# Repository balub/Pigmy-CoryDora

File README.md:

# Pigmy Corydora

A compact 3-key macropad built around the [Glyph Mini RP2040](https://shop.pcbcupid.com/product/gdm001). Designed for desk use as a shortcut pad, mute button, or media controller small enough to stay out of the way.

**[Build Guide →](https://www.notion.so/Pigmy-CoryDora-Build-Guide-36b9d3177a9b804fbc1ad1b240c95a71?source=copy_link)**

## Features

- 3× Cherry MX-compatible switches
- 2× WS2812B RGB LEDs
- Glyph Mini RP2040 (PCB Cupid) (RP2040, USB-C, onboard LED)
- 4× M2 mounting holes for case attachment
- Hand-solderable SMD components (1206 caps)

## Bill of Materials

| Ref | Component | Qty |
|-----|-----------|-----|
| RZ1 | Glyph Mini RP2040 (PCB Cupid) | 1 |
| SW1–SW3 | Cherry MX-compatible switch | 3 |
| D1–D2 | WS2812B LED (PLCC-4, 5×5mm) | 2 |
| R1 | 330Ω resistor (1206) | 1 |
| C1, C2 | 100nF capacitor (1206) | 2 |
| H1–H4 | M2 mounting hardware | 4 |

## PCB

Designed in KiCad 8. Gerbers can be generated from `pigmy-corydora.kicad_pcb` and sent to any PCB fab (Lions Circuit, JLCPCB, PCBWay, etc.).

## License

Hardware design files are released under [CERN-OHL-P v2](https://ohwr.org/cern_ohl_p_v2.txt).

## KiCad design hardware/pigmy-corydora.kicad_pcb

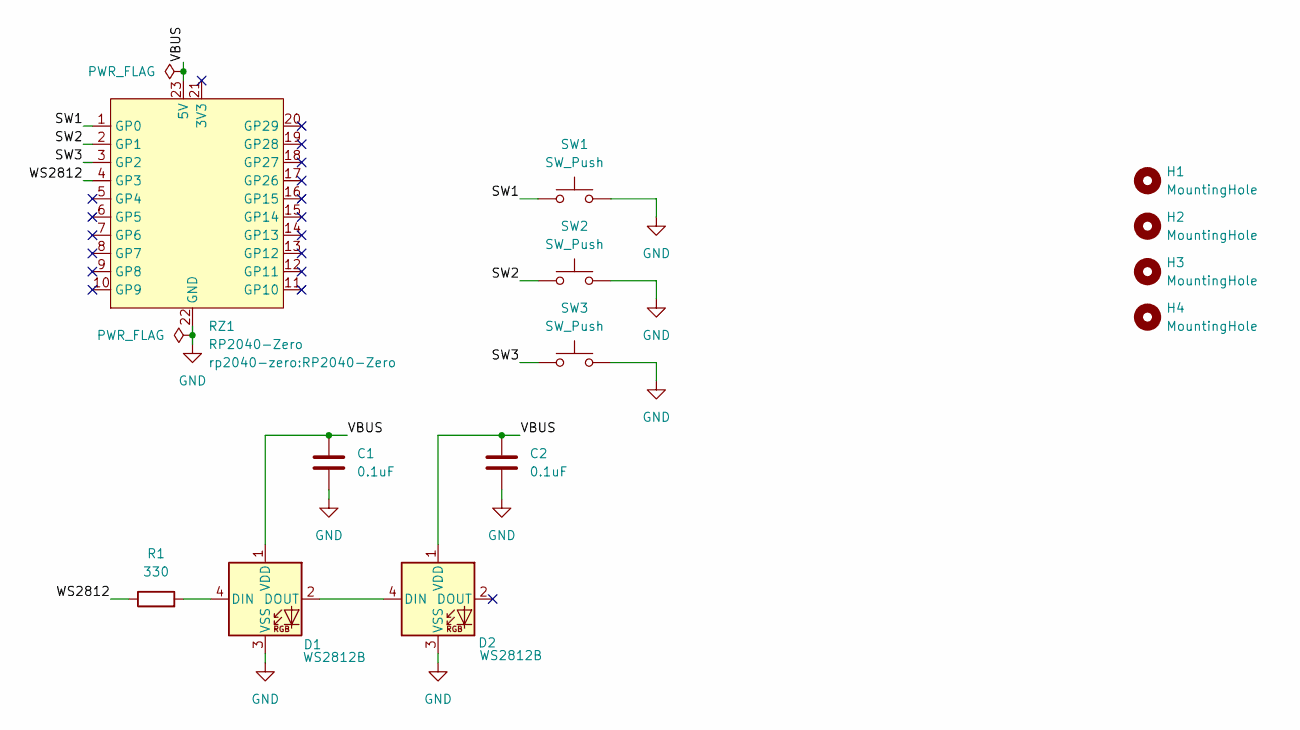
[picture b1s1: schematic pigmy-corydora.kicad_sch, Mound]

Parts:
C1, C2: 0.1uF; C_1206_3216Metric_Pad1.33x1.80mm_HandSolder
D1, D2: WS2812B; LED_WS2812B_PLCC4_5.0x5.0mm_P3.2mm
H1, H2, H3, H4: MountingHole; MountingHole_2.2mm_M2_DIN965_Pad
R1: 330; R_1206_3216Metric_Pad1.30x1.75mm_HandSolder
RZ1: RP2040-Zero
SW1, SW2, SW3: SW_Push; SW_Cherry_MX_PCB_1.00u

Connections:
/SW1: RZ1.1 (GP0), SW1.1
/SW2: RZ1.2 (GP1), SW2.1
/SW3: RZ1.3 (GP2), SW3.1
/VBUS: C1.1, C2.1, D1.1 (VDD), D2.1 (VDD), RZ1.23 (5V)
/WS2812: R1.1, RZ1.4 (GP3)
GND: C1.2, C2.2, D1.3 (VSS), D2.3 (VSS), RZ1.22 (GND), SW1.2, SW2.2, SW3.2
unnamed: D1.4 (DIN), R1.2
unnamed: D1.2 (DOUT), D2.4 (DIN)

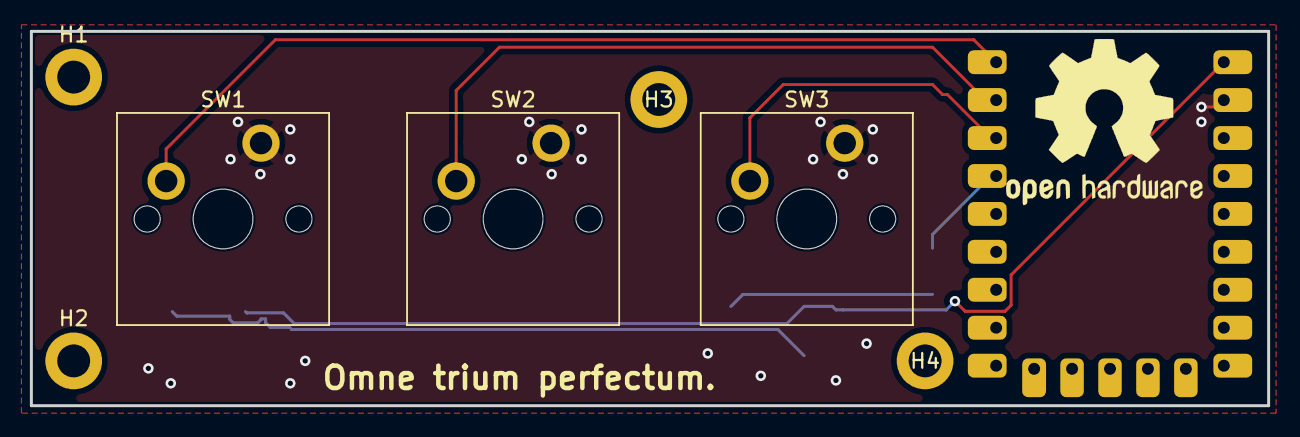
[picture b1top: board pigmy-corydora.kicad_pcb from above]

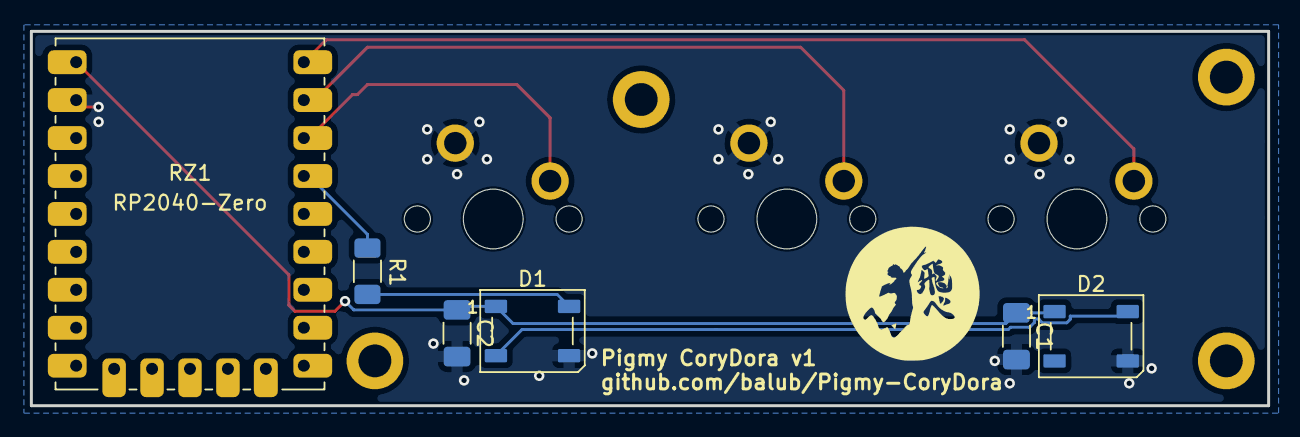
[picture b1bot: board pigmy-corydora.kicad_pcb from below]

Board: 2 copper layers, 82.8 x 25.1 mm, 14 parts (7 on the bottom side), 8 nets.

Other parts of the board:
d: LOGO; Tobe_logo

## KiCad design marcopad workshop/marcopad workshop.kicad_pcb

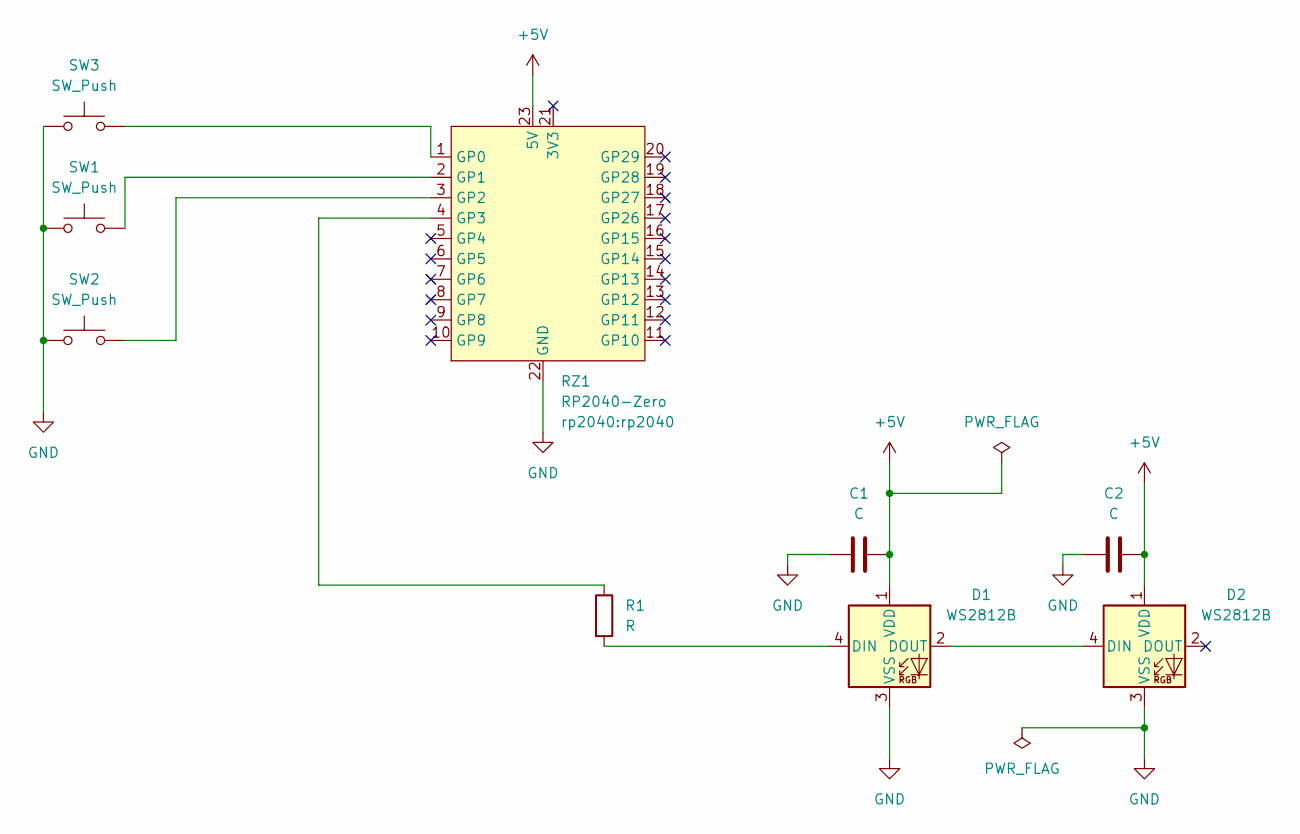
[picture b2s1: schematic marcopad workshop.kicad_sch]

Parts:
C1, C2: C; C_1210_3225Metric_Pad1.33x2.70mm_HandSolder
D1, D2: WS2812B; LED_WS2812B_PLCC4_5.0x5.0mm_P3.2mm
R1: R; R_0805_2012Metric_Pad1.20x1.40mm_HandSolder
RZ1: RP2040-Zero; rp2040
SW1, SW2, SW3: SW_Push; SW_Cherry_MX_1.00u_PCB

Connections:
+5V: C1.2, C2.2, D1.1 (VDD), D2.1 (VDD), RZ1.23 (5V)
GND: C1.1, C2.1, D1.3 (VSS), D2.3 (VSS), RZ1.22 (GND), SW1.1, SW2.1, SW3.1
unnamed: D1.4 (DIN), R1.2
unnamed: D1.2 (DOUT), D2.4 (DIN)
unnamed: RZ1.1 (GP0), SW3.2
unnamed: RZ1.2 (GP1), SW1.2
unnamed: RZ1.3 (GP2), SW2.2
unnamed: R1.1, RZ1.4 (GP3)

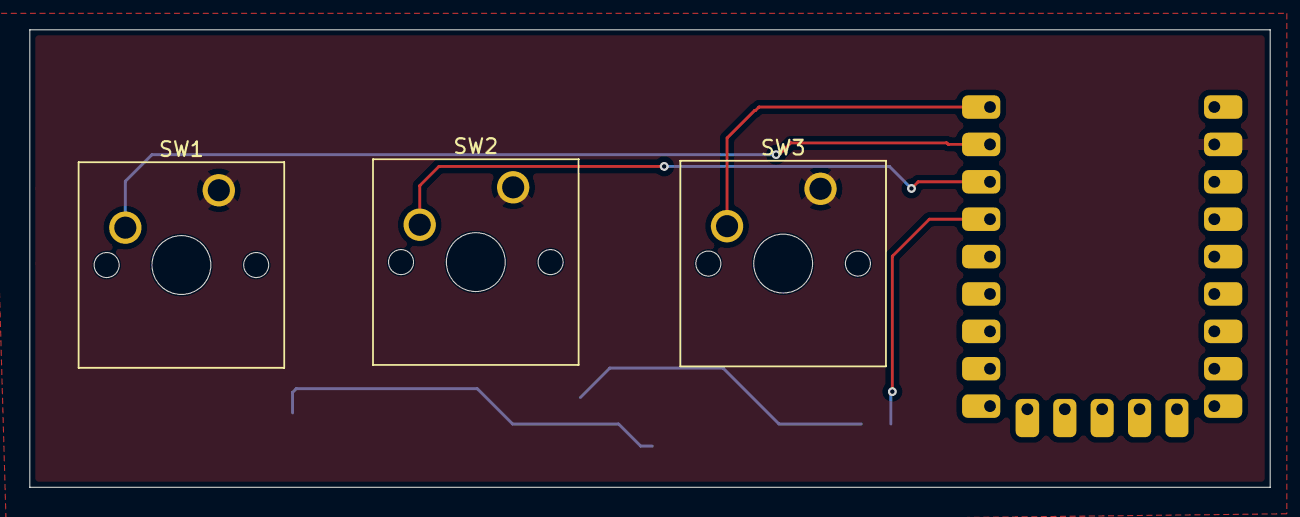
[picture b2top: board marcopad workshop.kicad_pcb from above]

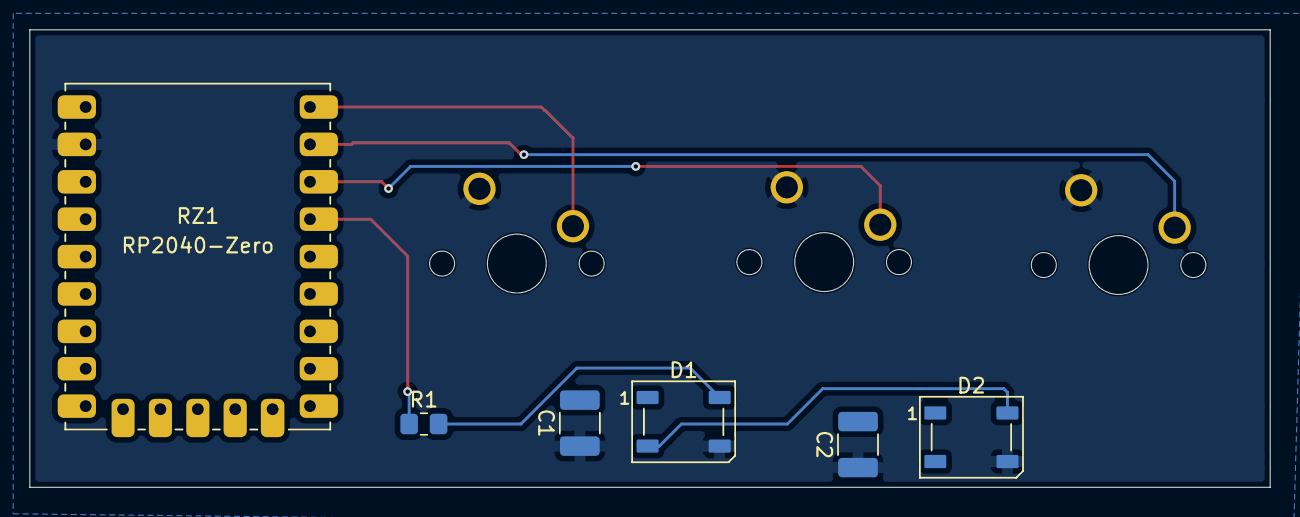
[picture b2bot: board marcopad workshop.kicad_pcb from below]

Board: 2 copper layers, 84.3 x 31.1 mm, 9 parts (6 on the bottom side), 8 nets.

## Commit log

2026-05-25 feat: added missing libs to firmware
2026-05-25 chore: removed macropad workshop files
2026-05-25 refactor: reorganize project into hardware/, cad/, firmware/
